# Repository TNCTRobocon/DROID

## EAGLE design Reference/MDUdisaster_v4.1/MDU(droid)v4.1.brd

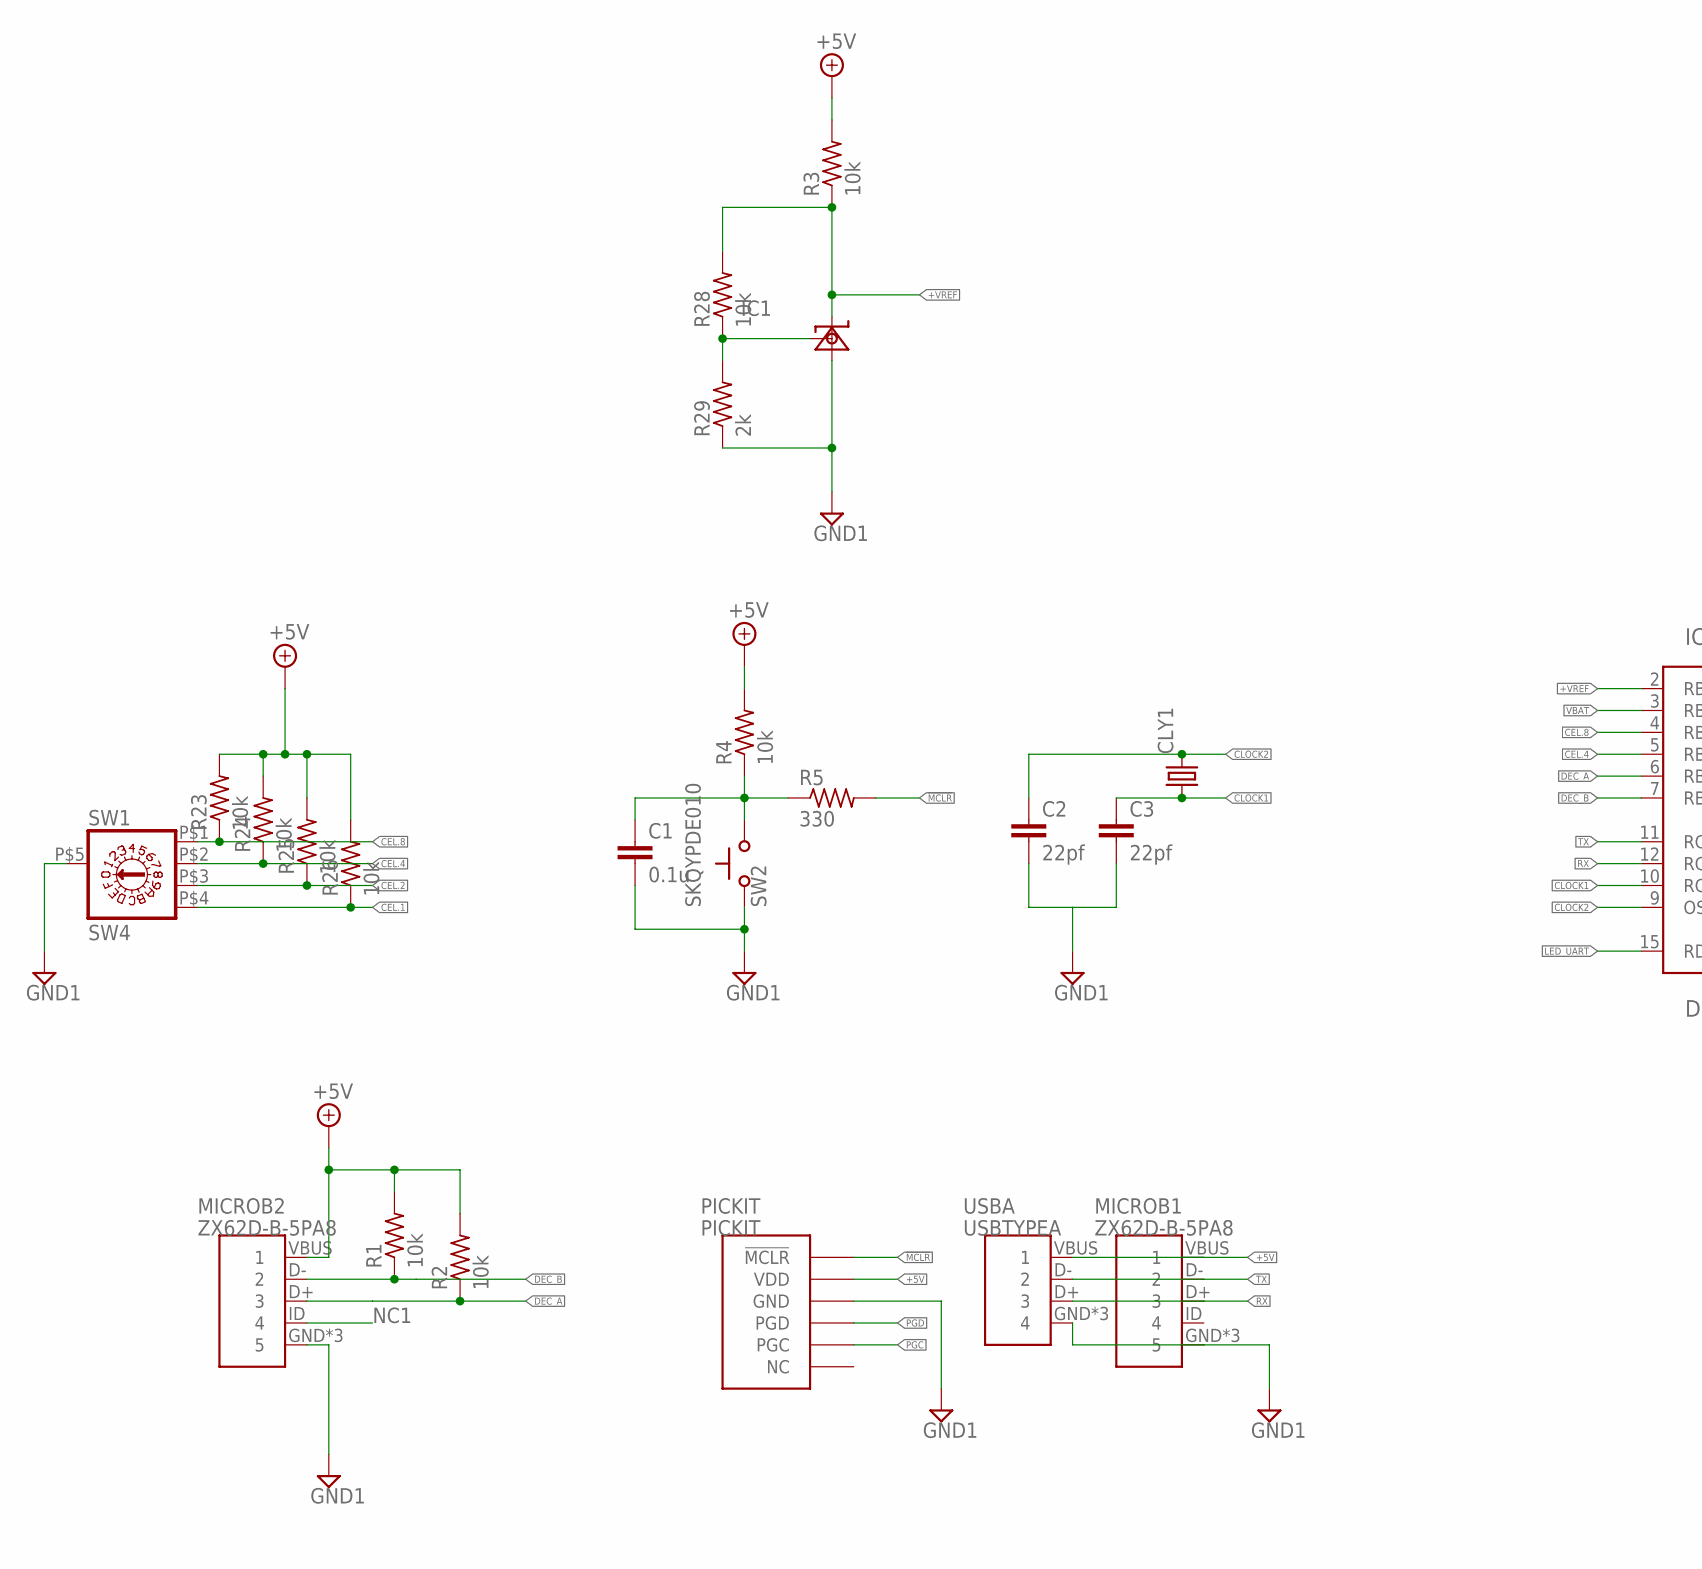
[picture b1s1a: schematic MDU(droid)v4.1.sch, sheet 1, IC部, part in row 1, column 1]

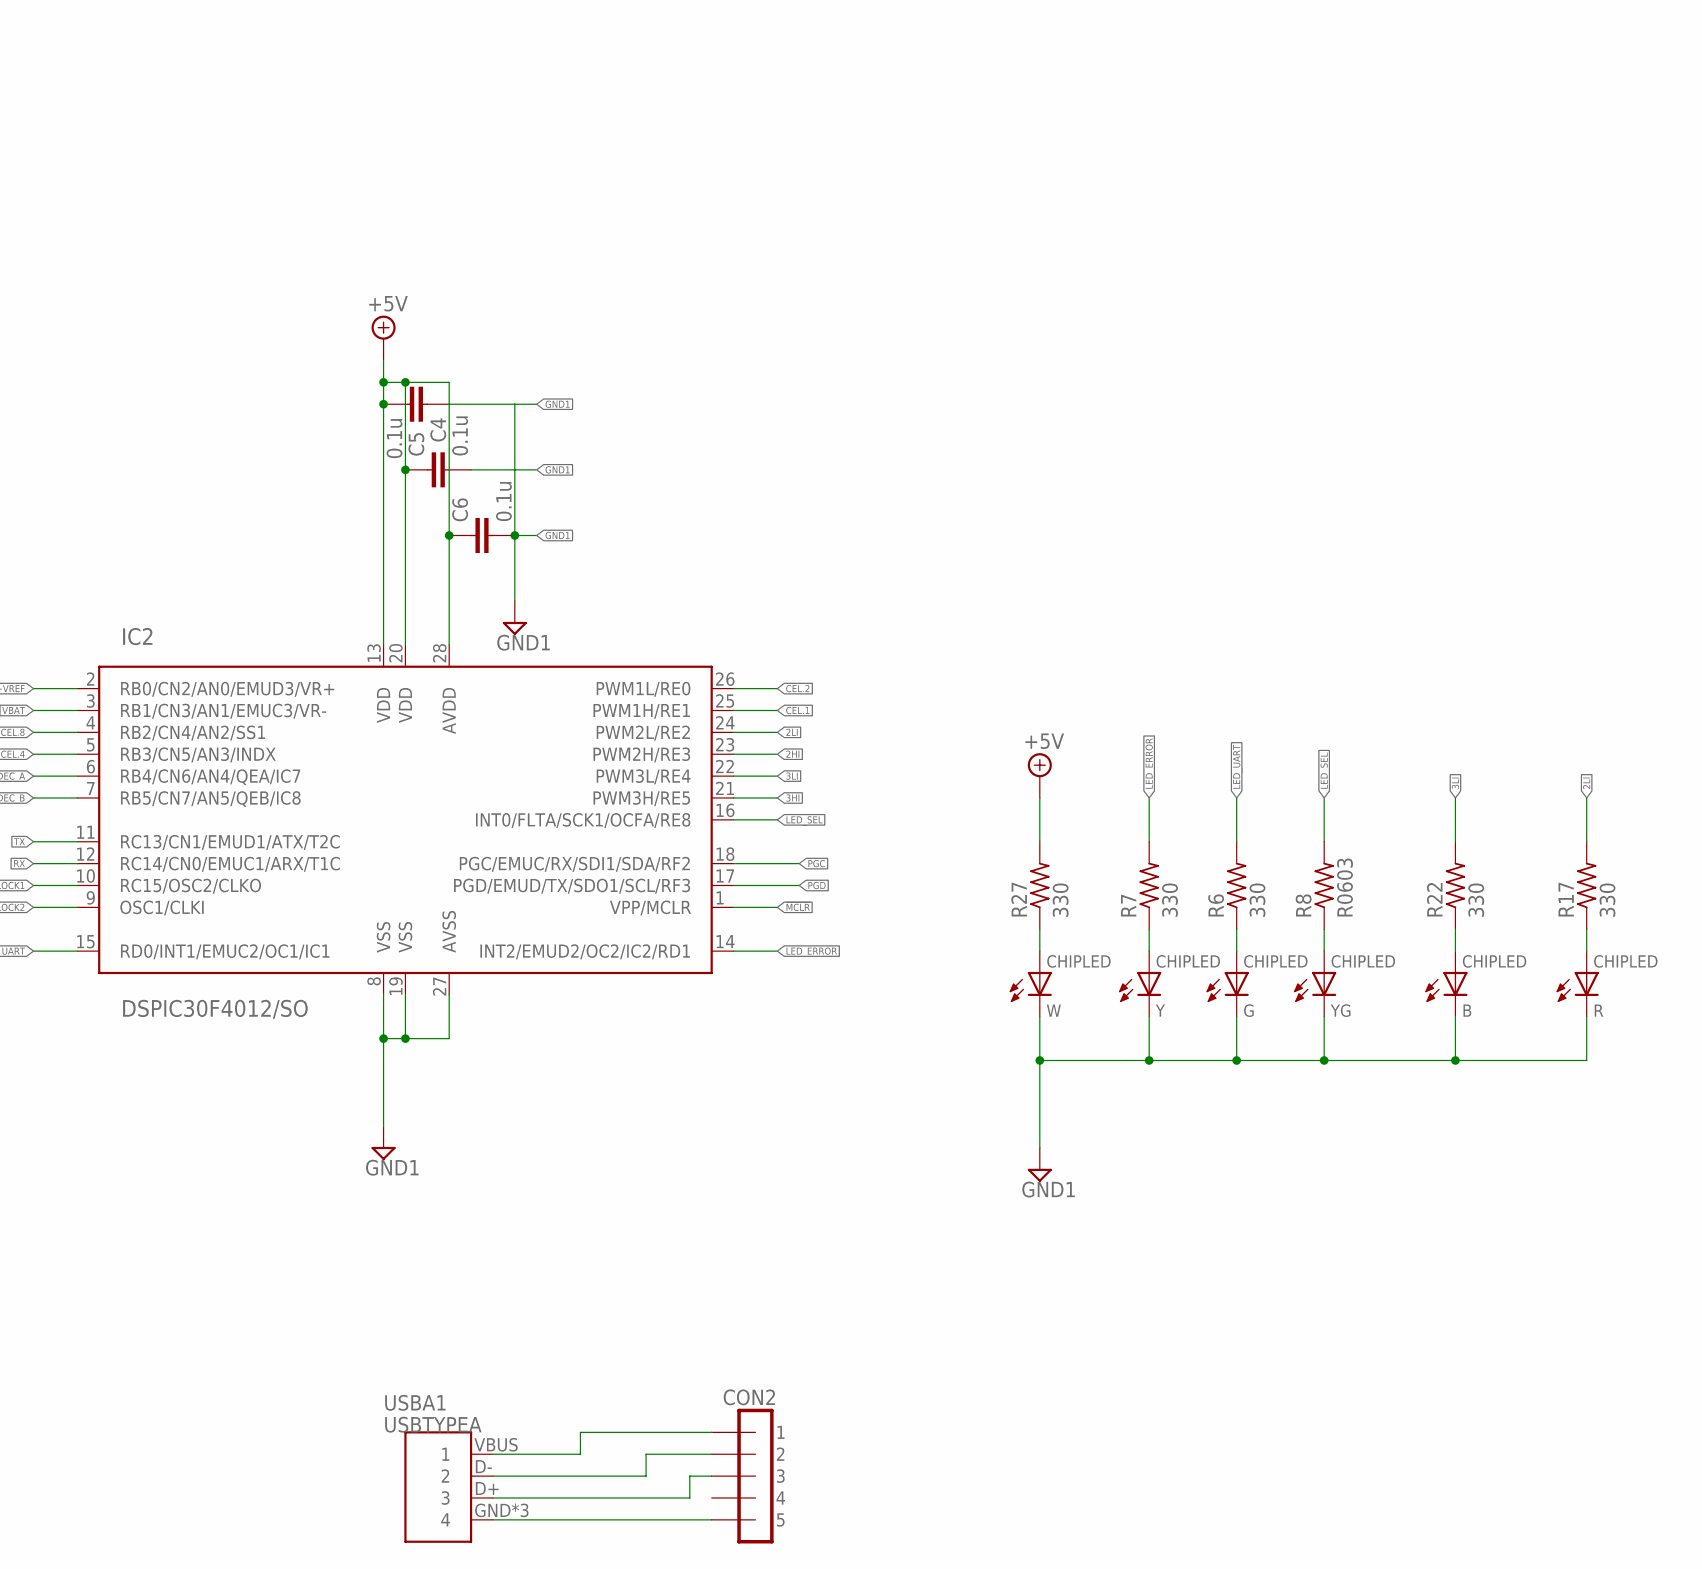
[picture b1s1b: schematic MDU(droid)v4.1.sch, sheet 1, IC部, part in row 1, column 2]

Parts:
B: CHIPLED; CHIPLED_0603
C1, C4, C5, C6: 0.1u; C0603
C2, C3: 22pf; C0603
CLY1: CRYSTALHC49S; HC49/S
CON2: CON-5; 5-L
G: CHIPLED; CHIPLED_0603
IC1: TA76431F; SOT89
IC2: DSPIC30F4012/SO; SO-28W
MICROB1, MICROB2: ZX62D-B-5PA8; USB-B-MICRO-SMD
PICKIT: PICKIT; 1X06
R: CHIPLED; CHIPLED_0603
R1, R2, R3, R4, R23, R24, R25, R26, R28: 10k; R0603
R5, R6, R7, R17, R22, R27: 330; R0603
R8: R0603
R29: 2k; R0603
SW1: SW4; DRS3016
SW2: SKQYPDE010
USBA, USBA1: USBTYPEA; USB-A-H
W: CHIPLED; CHIPLED_0603
Y: CHIPLED; CHIPLED_0603
YG: CHIPLED; CHIPLED_0603

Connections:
2HI: IC2.23 (PWM2H/RE3); also elsewhere on the board
2LI: IC2.24 (PWM2L/RE2), R17.2; also elsewhere on the board
3HI: IC2.21 (PWM3H/RE5); also elsewhere on the board
3LI: IC2.22 (PWM3L/RE4), R22.2; also elsewhere on the board
!MCLR: IC2.1 (VPP/MCLR), PICKIT.1 (!MCLR), R5.2
+5V: C4.2, C5.1, C6.1, IC2.13 (VDD), IC2.20 (VDD), IC2.28 (AVDD), MICROB1.VBUS (1), MICROB2.VBUS (1), PICKIT.2 (VDD), R1.2, R2.2, R3.2, R4.2, R23.2, R24.2, R25.2, R26.2, R27.2, USBA.VBUS (1)
+VREF: IC1.1 (K), IC2.2 (RB0/CN2/AN0/EMUD3/VR+), R3.1, R28.2
CEL.1: IC2.25 (PWM1H/RE1), R26.1, SW1.P$4 (8)
CEL.2: IC2.26 (PWM1L/RE0), R25.1, SW1.P$3 (4)
CEL.4: IC2.5 (RB3/CN5/AN3/INDX), R24.1, SW1.P$2 (2)
CEL.8: IC2.4 (RB2/CN4/AN2/SS1), R23.1, SW1.P$1 (1)
CLOCK1: C3.1, CLY1.1, IC2.10 (RC15/OSC2/CLKO)
CLOCK2: C2.1, CLY1.2, IC2.9 (OSC1/CLKI)
DEC_A: IC2.6 (RB4/CN6/AN4/QEA/IC7), MICROB2.D+ (3), R2.1
DEC_B: IC2.7 (RB5/CN7/AN5/QEB/IC8), MICROB2.D- (2), R1.1
GND1: B.C, C1.2, C2.2, C3.2, C4.1, C5.2, C6.2, G.C, IC1.2 (A), IC1.2@1 (A), IC2.8 (VSS), IC2.19 (VSS), IC2.27 (AVSS), MICROB1.GND (5), MICROB1.SHIELD1 (5), MICROB1.SHIELD2 (5), MICROB2.GND (5), MICROB2.SHIELD1 (5), MICROB2.SHIELD2 (5), PICKIT.3 (GND), R.C, R29.1, SW1.P$5 (C), SW2.SW1, USBA.GND (4), USBA.SHLD1 (4), USBA.SHLD2 (4), W.C, Y.C, YG.C; also elsewhere on the board
LED_ERROR: IC2.14 (INT2/EMUD2/OC2/IC2/RD1), R7.2
LED_SEL: IC2.16 (INT0/FLTA/SCK1/OCFA/RE8), R8.2
LED_UART: IC2.15 (RD0/INT1/EMUC2/OC1/IC1), R6.2
MCLR: C1.1, R4.1, R5.1, SW2.SW2
unnamed: R27.1, W.A
unnamed: G.A, R6.1
unnamed: R8.1, YG.A
unnamed: IC1.3 (REF), R28.1, R29.2
unnamed: CON2.P$1 (1), USBA1.VBUS (1)
unnamed: CON2.P$5 (5), USBA1.GND (4), USBA1.SHLD1 (4), USBA1.SHLD2 (4)
unnamed: CON2.P$2 (2), USBA1.D- (2)
unnamed: R7.1, Y.A
unnamed: R.A, R17.1
unnamed: B.A, R22.1
unnamed: CON2.P$3 (3), USBA1.D+ (3)
NC1: MICROB2.ID (4)
PGC: IC2.18 (PGC/EMUC/RX/SDI1/SDA/RF2), PICKIT.5 (PGC)
PGD: IC2.17 (PGD/EMUD/TX/SDO1/SCL/RF3), PICKIT.4 (PGD)
RX: IC2.12 (RC14/CN0/EMUC1/ARX/T1C), MICROB1.D+ (3), USBA.D+ (3)
TX: IC2.11 (RC13/CN1/EMUD1/ATX/T2C), MICROB1.D- (2), USBA.D- (2)
VBAT: IC2.3 (RB1/CN3/AN1/EMUC3/VR-); also elsewhere on the board

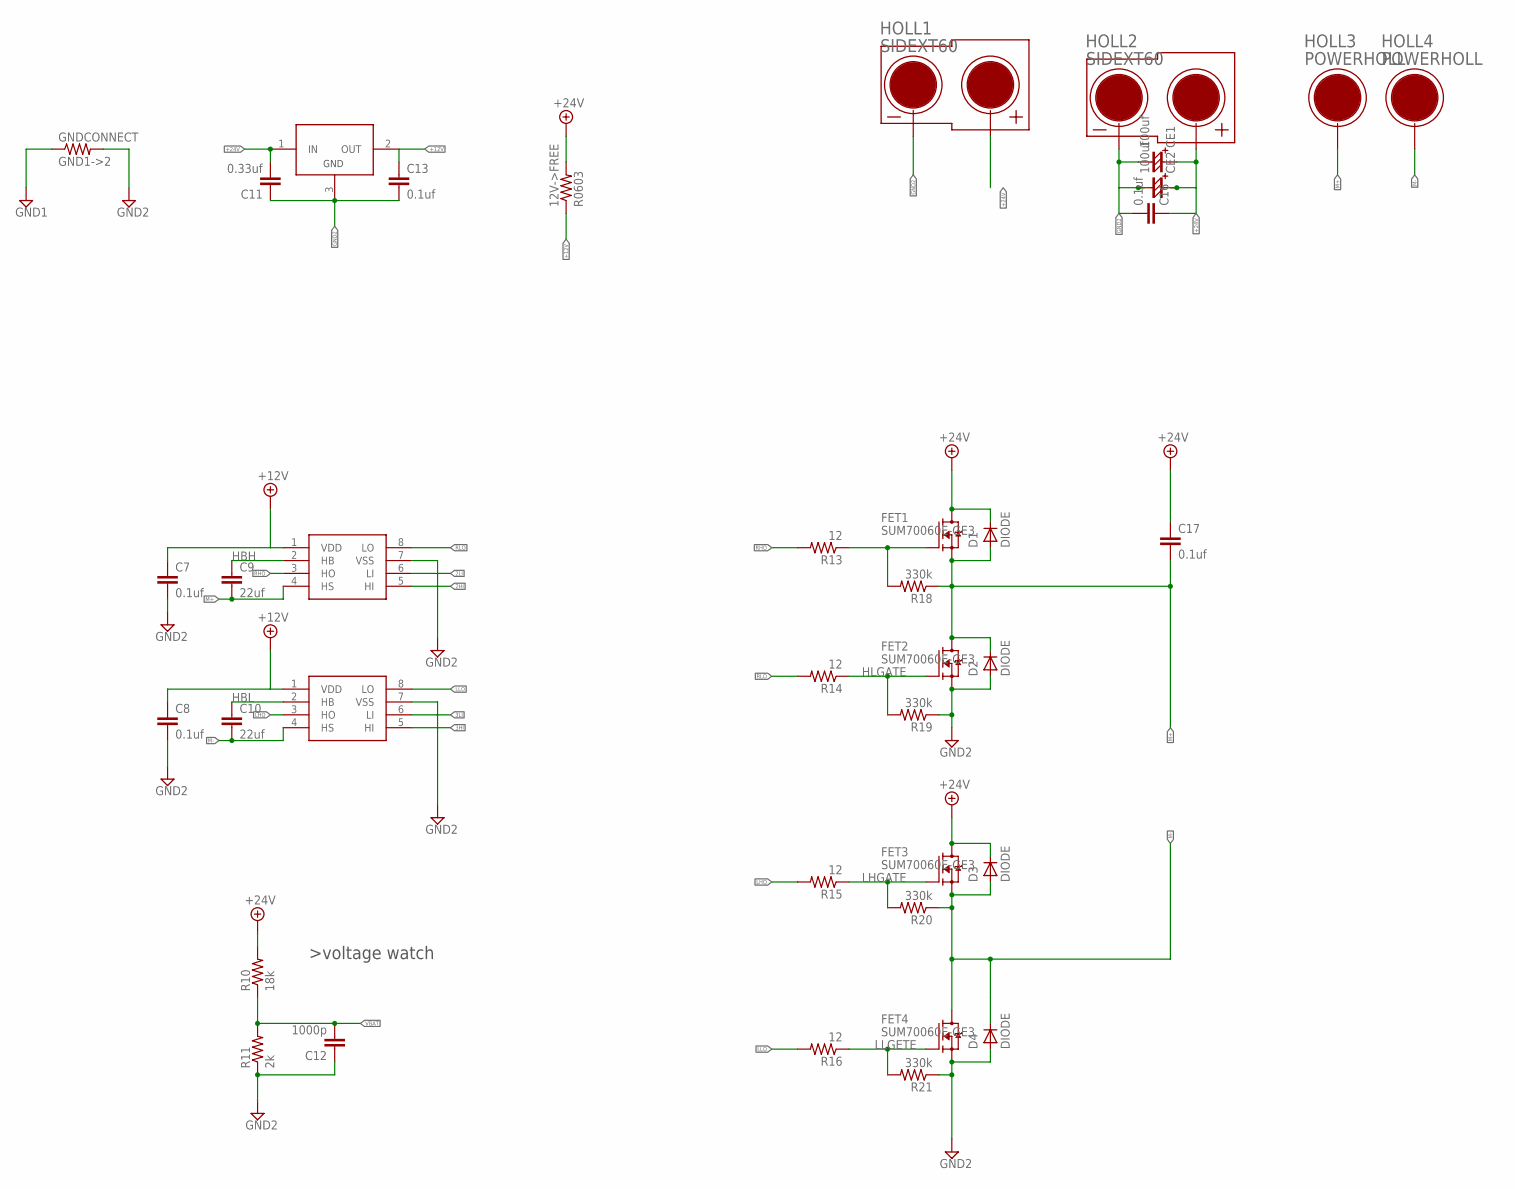
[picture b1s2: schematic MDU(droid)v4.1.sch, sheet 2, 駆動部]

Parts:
12V->FREE: R0603
C7, C8, C13, C16, C17: 0.1uf; C0603
C9, C10: 22uf; C0603
C11: 0.33uf; C0603
C12: 1000p; C0603
CE1, CE2: 100uf; CE1
D1, D2, D3, D4: DIODE; DO35-7A
FET1, FET2, FET3, FET4: SUM70060E-GE3; TO263AB
GNDCONNECT: GND1->2; R0603
HOLL1, HOLL2: SIDEXT60
HOLL3, HOLL4: POWERHOLL
IC3: MC7812BD2TG; TO263
IC5: MIC4604; SOIC8
MIC4604: MIC4604; SOIC8
R10: 18k; R0603
R11: 2k; R0603
R13, R14, R15, R16: 12; R0603
R18, R19, R20, R21: 330k; R0603

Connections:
2HI: MIC4604.5 (HI); also elsewhere on the board
2LI: MIC4604.6 (LI); also elsewhere on the board
3HI: IC5.5 (HI); also elsewhere on the board
3LI: IC5.6 (LI); also elsewhere on the board
+12V: 12V->FREE.1, C7.1, C8.1, C13.1, IC3.2 (OUT), IC5.1 (VDD), MIC4604.1 (VDD)
+24V: 12V->FREE.2, C11.2, C16.1, C17.1, CE1.1 (A), CE2.1 (A), D1.C, D3.C, FET1.K (D), FET3.K (D), HOLL1.P$2, HOLL1.P$4, HOLL2.P$2, HOLL2.P$4, IC3.1 (IN), R10.2
FETHHGATE: FET1.1 (G), R13.1, R18.2
GND1: GNDCONNECT.1; also elsewhere on the board
GND2: C7.2, C8.2, C11.1, C12.1, C13.2, C16.2, CE1.2 (C), CE2.2 (C), D2.A, D4.A, FET2.2 (S), FET4.2 (S), GNDCONNECT.2, HOLL1.P$1, HOLL1.P$3, HOLL2.P$1, HOLL2.P$3, IC3.3 (GND), IC5.7 (VSS), MIC4604.7 (VSS), R11.1, R19.1, R21.1
HBH: C9.1, MIC4604.2 (HB)
HBL: C10.1, IC5.2 (HB)
HLGATE: FET2.1 (G), R14.1, R19.2
LHGATE: FET3.1 (G), R15.1, R20.2
LHO: IC5.3 (HO), R15.2
LLGETE: FET4.1 (G), R16.1, R21.2
LLO: IC5.8 (LO), R16.2
M+: C9.2, C17.2, D1.A, D2.C, FET1.2 (S), FET2.K (D), HOLL3.P$1, MIC4604.4 (HS), R18.1
M-: C10.2, D3.A, D4.C, FET3.2 (S), FET4.K (D), HOLL4.P$1, IC5.4 (HS), R20.1
RHO: MIC4604.3 (HO), R13.2
RLO: MIC4604.8 (LO), R14.2
VBAT: C12.2, R10.1, R11.2; also elsewhere on the board

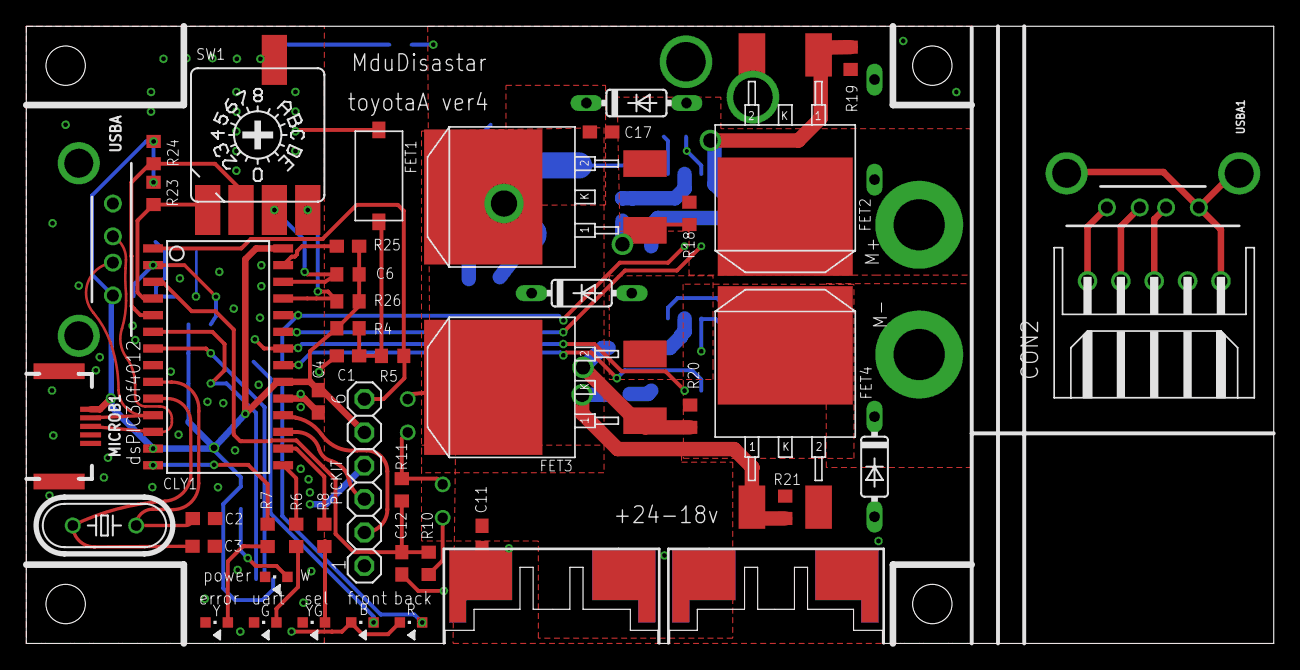
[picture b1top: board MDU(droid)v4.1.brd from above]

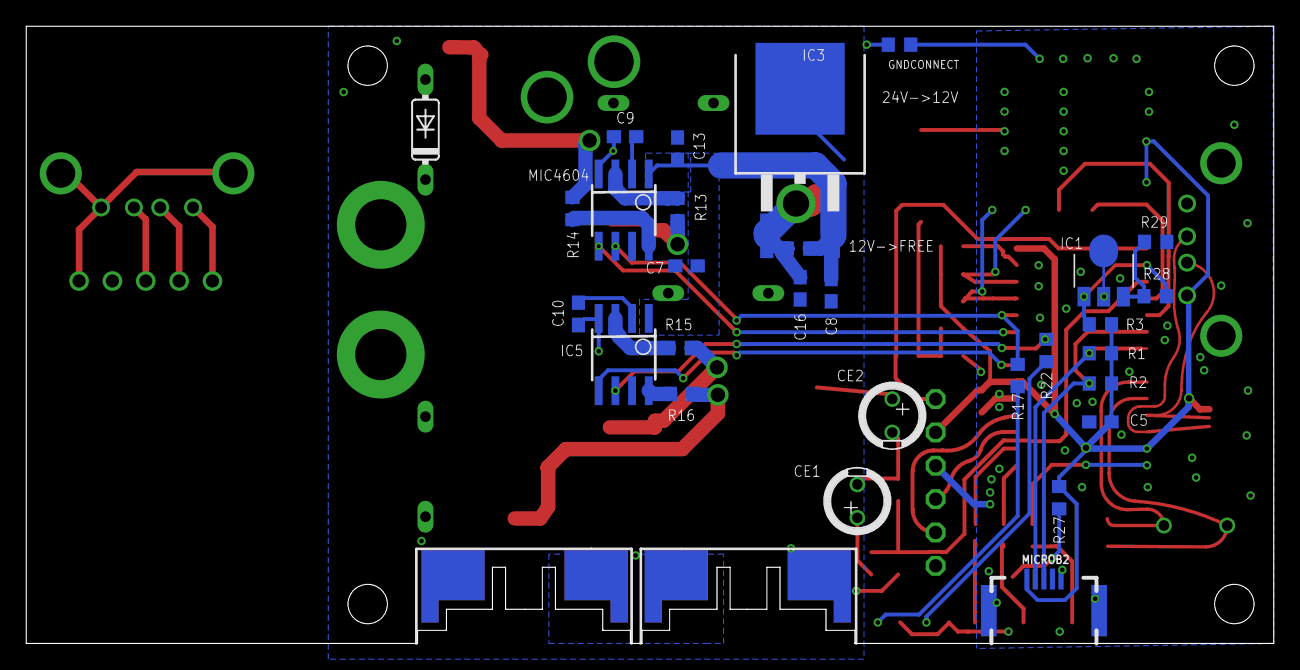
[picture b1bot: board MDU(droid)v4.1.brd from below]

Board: 2 copper layers, 95.0 x 47.0 mm, 78 parts (30 on the bottom side), 51 nets.

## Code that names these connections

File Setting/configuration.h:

/* 
 * File:   configuration.h
 * Author: TERU
 *
 * Created on 2016/03/23, 0:16
 */

#ifndef CONFIGURATION_H
#define	CONFIGURATION_H


//デバイス環境
#include "p30F4012.h"


//環境構築
#define FORIG (1000000UL)
#define FOSC (FORIG*8/4) //10[MHz]*8[PLL]/4[DIV]=20[MHz] 

//10MHz*8(PLL)/4(divsion))

//デバイスを選択する
#define DEVICE_COMMON
//#define DEVICE_DRAGON
#define ADC_USE
#if defined(DEVICE_COMMON)
#define PORT_TYPE_A
#elif defined(DEVICE_DRAGON)
#define PORT_TYPE_B

#endif


//アドレス取得　ピン配置
#if defined(PORT_TYPE_A)
#define PIN_SEL1() PORTBbits.RB2
#define PIN_SEL2() PORTEbits.RE8
#define PIN_SEL4() PORTEbits.RE0
#define PIN_SEL8() PORTEbits.RE1
#define TRIS_SEL1(X) TRISBbits.TRISB2=(X)
#define TRIS_SEL2(X) TRISEbits.TRISE8=(X)
#define TRIS_SEL4(X) TRISEbits.TRISE0=(X)
#define TRIS_SEL8(X) TRISEbits.TRISE1=(X)
#elif defined(PORT_TYPE_B)

//TODO ピン配置を設定する
#endif
//Stoper
#define SW_ST()   PORTEbits.RE8

//LED
#define LED_RX      LATDbits.LATD0
#define LED_TX      LATDbits.LATD1
#define LED_ERROR   LATDbits.LATD1
#define LED_APP     LATBbits.LATB2

#define PIN_HIGH(x) ((x)=true)
#define PIN_LOW(x)  ((x)=false)
#define PIN_INV(x)  ((x)=(^x))

//PWM
#define ST_PIN      LATEbits.LATE4
//UART
#define RX_BUFFER_SIZE  (64) //受信バッファの一つ当たりの大きさ
#define TX_BUFFER_SIZE  (64)
#define CMD_LENGTH (32)        // システムが受け入れられる文字の最大数、
#define CMD_MAX     (16)        // 最大分割数(1LINEあたり)
#define FILE_MAX    (32)        // 最大ファイル数
#define MULTI_MAX (8) //同時に実行できるコマンドの最大値
#define WORD_MAX (32)
#define PATH_DEPTH_MAX (8)
#define QUICK_MAX (8) 
#define WORD_MAX (32)
#define SYSTEM_SIZE (32)        //  システムに登録できる機能数

//EEPROM
#define EEPROM_BUFFER_SIZE (64) //EEPROMの書き込み用バッファ

//ADC





#endif	/* CONFIGURATION_H */

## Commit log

2018-06-21 PUSHしてみました
2018-06-21 first contact
2018-06-21 add .gitignore
2018-07-08 Revert "PWMは設定済み ADCの設定を追加 サンプリング周期を決めたい"
    This reverts commit 5923e85938e03e0fd10f93974be49abbf8182944.
2018-07-10 ADの設定を追加
2018-07-12 pid処理を追加 動作確認はしていない
2018-07-13 make submodule of eshell
2018-07-16 motor.cとmotor.hをappに移動 EShellを移植
2018-07-19 no message
2018-08-23 バッテリ監視用コマンドbtypeを追加
2018-08-23 motor.cとmotor.hを追加（なぜか追加されていなかった）
2018-08-24 gitignoreを追加
2018-08-24 佐藤君のモタドラからコマンドを移植
2018-08-24 バッテリーチェック用のコマンド check 追加
2018-08-25 関数の名前を変更
2018-08-25 gitignore のtest
2018-08-25 nbproject を切った
2018-08-25 余計なファイルを切れたはず
2018-08-26 project cloned
2018-08-26 add gitignore
2018-08-26 余計なファイルの追跡を削除
2018-08-27 sel の設定を追加 dtコマンドがはじかれるようになった
2018-08-27 モーターの正転動作を確認
2018-08-28 佐藤君のプログラムからコマンドを移植
2018-08-29 コマンドがはじかれないことを確認
2018-08-30 program update
2018-08-31 バグの修正
2018-09-04 Add files via upload
    ファイル構成を変更
2018-09-04 バグを修正
2018-09-06 モーターの正転、逆転の動作を確認
2018-09-09 データシート、回路図を追加
